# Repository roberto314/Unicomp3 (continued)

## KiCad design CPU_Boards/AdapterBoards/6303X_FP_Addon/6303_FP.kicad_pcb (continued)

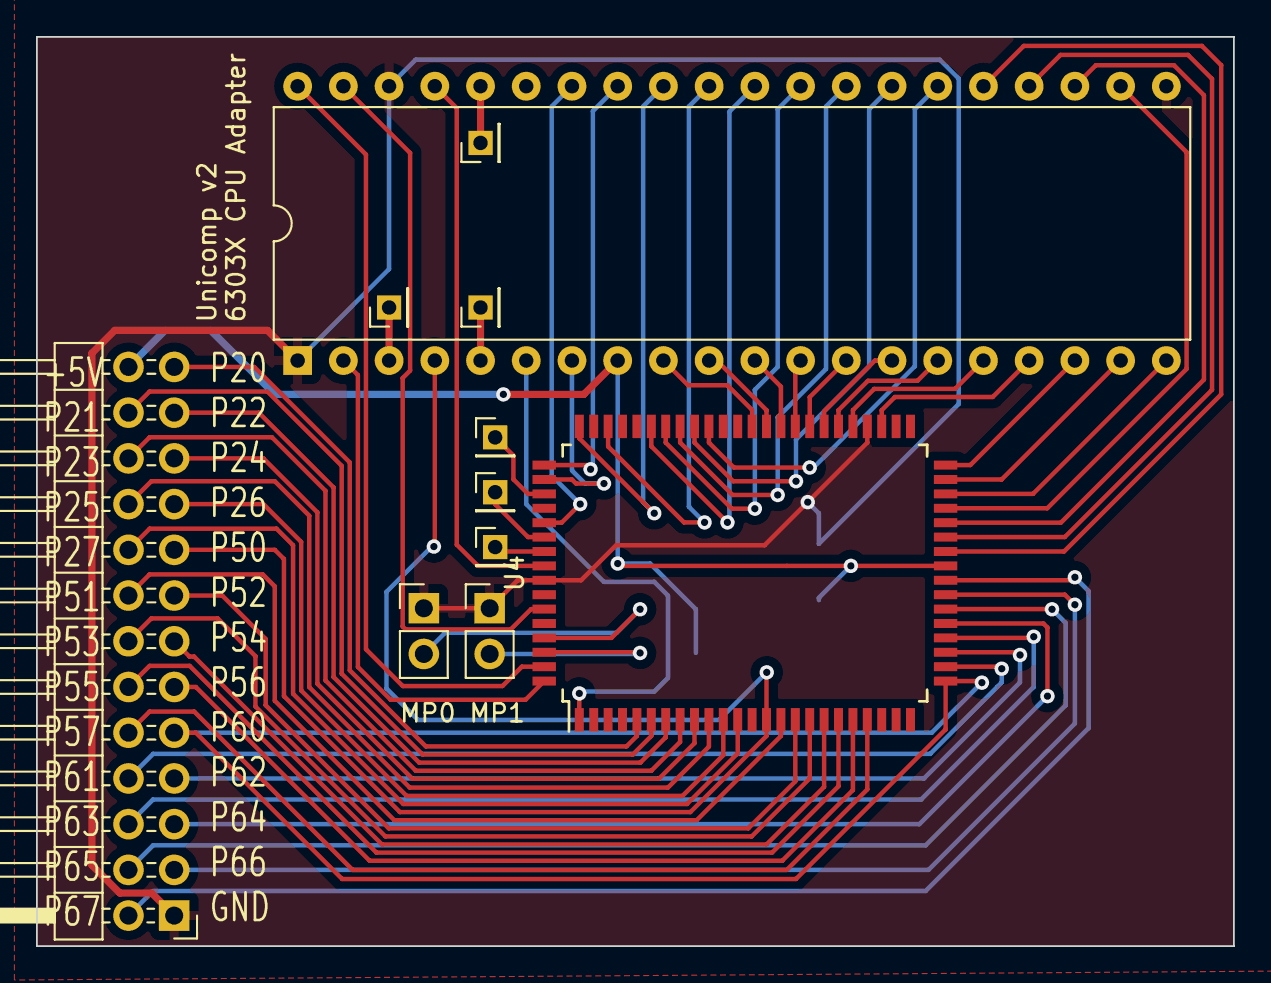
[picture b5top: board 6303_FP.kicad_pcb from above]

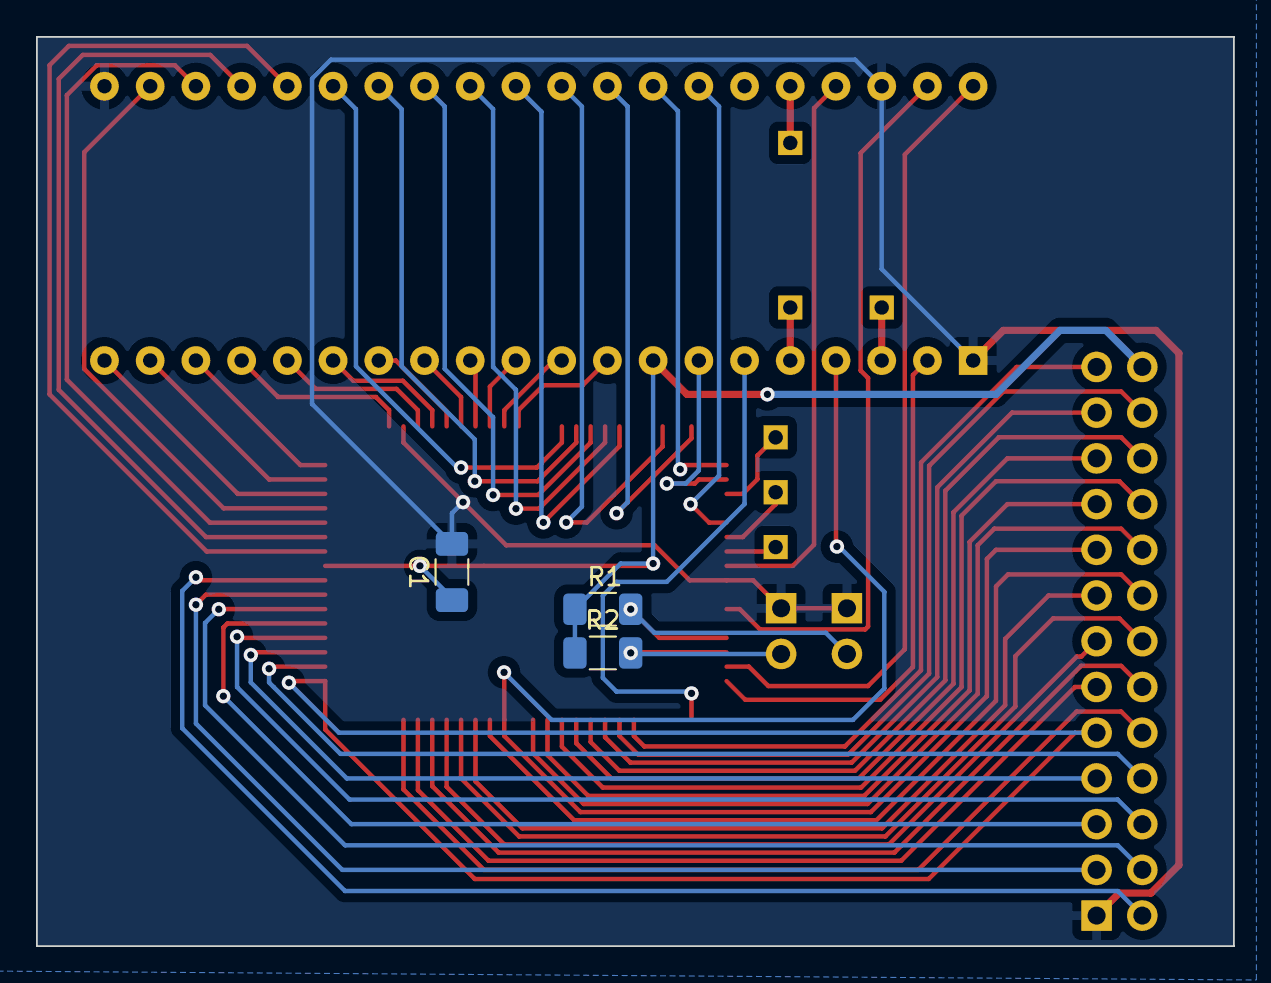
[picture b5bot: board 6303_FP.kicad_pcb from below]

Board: 2 copper layers, 66.5 x 50.5 mm, 14 parts (3 on the bottom side), 65 nets.

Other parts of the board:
U3: MC6802; DIP-40_W15.24mm

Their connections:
+5V: U3.8 (VCC); also elsewhere on the board
/A0: U3.9 (A0); also elsewhere on the board
/A1: U3.10 (A1); also elsewhere on the board
/A2: U3.11 (A2); also elsewhere on the board
/A3: U3.12 (A3); also elsewhere on the board
/A4: U3.13 (A4); also elsewhere on the board
/A5: U3.14 (A5); also elsewhere on the board
/A6: U3.15 (A6); also elsewhere on the board
/A7: U3.16 (A7); also elsewhere on the board
/A8: U3.17 (A8); also elsewhere on the board
/A9: U3.18 (A9); also elsewhere on the board
/A10: U3.19 (A10); also elsewhere on the board
/A11: U3.20 (A11); also elsewhere on the board
/A12: U3.22 (A12); also elsewhere on the board
/A13: U3.23 (A13); also elsewhere on the board
/A14: U3.24 (A14); also elsewhere on the board
/A15: U3.25 (A15); also elsewhere on the board
/BA: U3.7 (BA); also elsewhere on the board
/CPUCLK: U3.39 (EXTAL); also elsewhere on the board
/D0: U3.33 (D0); also elsewhere on the board
/D1: U3.32 (D1); also elsewhere on the board
/D2: U3.31 (D2); also elsewhere on the board
/D3: U3.30 (D3); also elsewhere on the board
/D4: U3.29 (D4); also elsewhere on the board
/D5: U3.28 (D5); also elsewhere on the board
/D6: U3.27 (D6); also elsewhere on the board
/D7: U3.26 (D7); also elsewhere on the board
/PHI2: U3.37 (E); also elsewhere on the board
/R/~W: U3.34 (R/~W); also elsewhere on the board
/~HALT: U3.2 (~HALT); also elsewhere on the board
/~IRQ1: U3.4 (~IRQ); also elsewhere on the board
/~NMI: U3.6 (~NMI); also elsewhere on the board
/~RST: U3.40 (~RESET); also elsewhere on the board
GND: U3.1 (VSS), U3.21 (VSS), U3.38 (XTAL); also elsewhere on the board
unnamed 63: U3.3 (MR); also elsewhere on the board
unnamed 64: U3.36 (RE); also elsewhere on the board
unnamed 65: U3.5 (VMA); also elsewhere on the board
